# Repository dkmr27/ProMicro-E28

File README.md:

# ProMicro-E28
A PCB for nRF52840 promicro using Ebyte E28-2G4MxxS modules

The production folder contains a .zip file suitable for PCB production (JLCPCB etc.)

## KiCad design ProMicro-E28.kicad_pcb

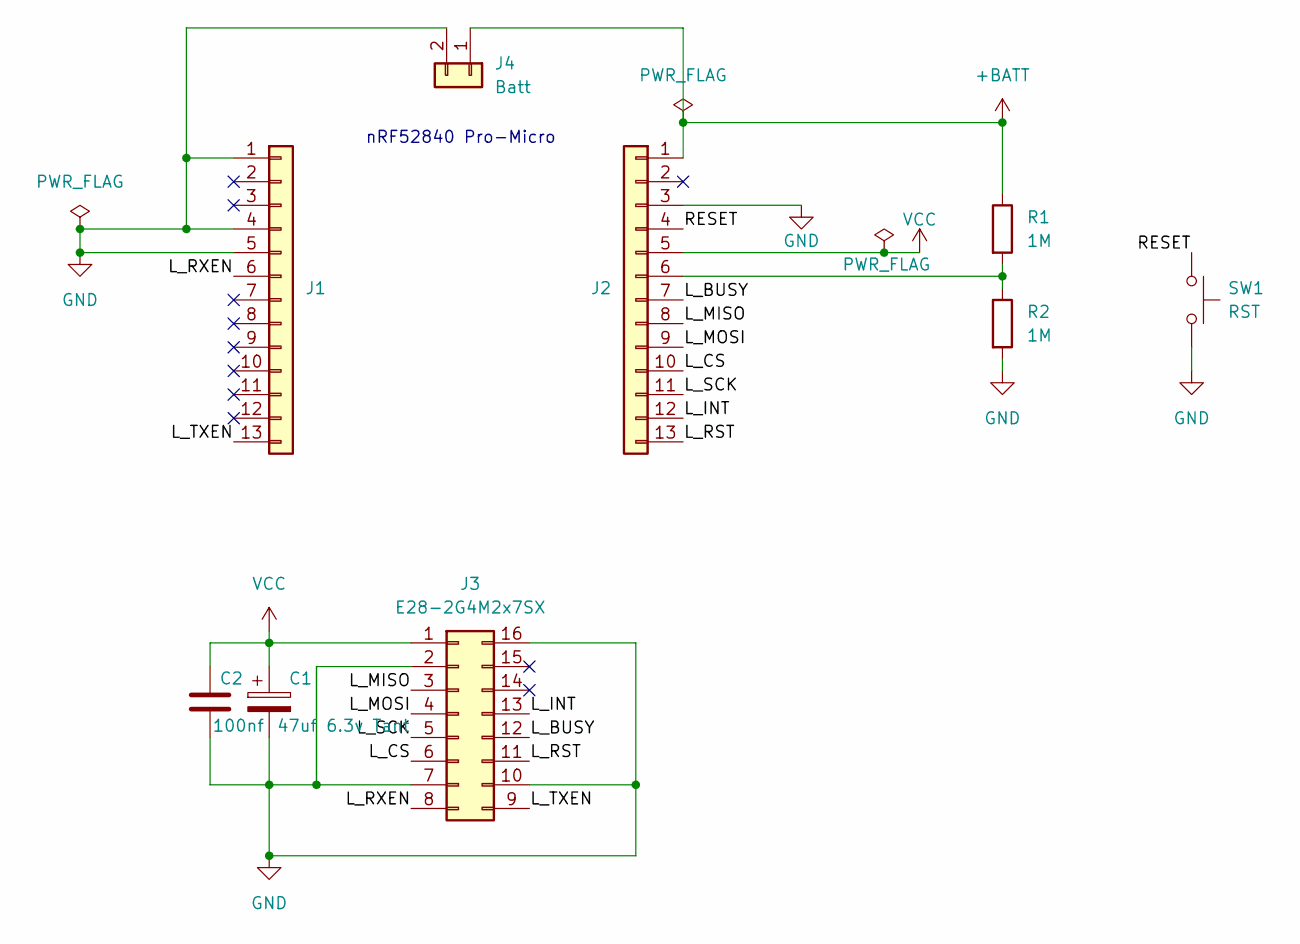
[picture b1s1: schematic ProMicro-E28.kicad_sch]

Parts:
C1: 47uf 6.3v Tant; CP_EIA-3528-21_Kemet-B_HandSolder
C2: 100nf; C_1206_3216Metric_Pad1.33x1.80mm_HandSolder
J1, J2: PinSocket_1x13_P2.54mm_Vertical
J3: E28-2G4M2x7SX; PE28(2G4M20SX)
J4: Batt; SolderWire-0.75sqmm_1x02_P4.8mm_D1.25mm_OD2.3mm
R1, R2: 1M; R_1206_3216Metric
SW1: RST; SW_SPST_TS-1088-xR020

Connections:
+BATT: J2.1, J4.1, R1.1
/L_BUSY: J2.7, J3.12
/L_CS: J2.10, J3.6
/L_INT: J2.12, J3.13
/L_MISO: J2.8, J3.3
/L_MOSI: J2.9, J3.4
/L_RST: J2.13, J3.11
/L_RXEN: J1.6, J3.8
/L_SCK: J2.11, J3.5
/L_TXEN: J1.13, J3.9
/RESET: J2.4, SW1.1
GND: C1.2, C2.2, J1.1, J1.4, J1.5, J2.3, J3.2, J3.7, J3.10, J3.16, J4.2, R2.2, SW1.2
unnamed: J2.6, R1.2, R2.1
VCC: C1.1, C2.1, J2.5, J3.1

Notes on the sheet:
nRF52840 Pro-Micro

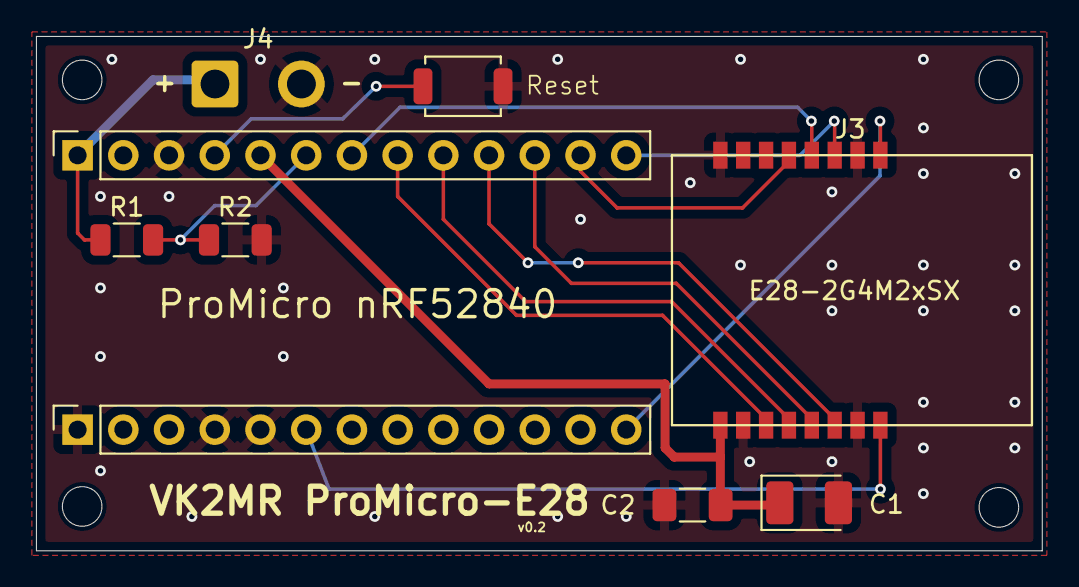
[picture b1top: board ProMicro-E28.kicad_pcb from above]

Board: 2 copper layers, 55.9 x 28.6 mm, 9 parts (0 on the bottom side), 14 nets.
